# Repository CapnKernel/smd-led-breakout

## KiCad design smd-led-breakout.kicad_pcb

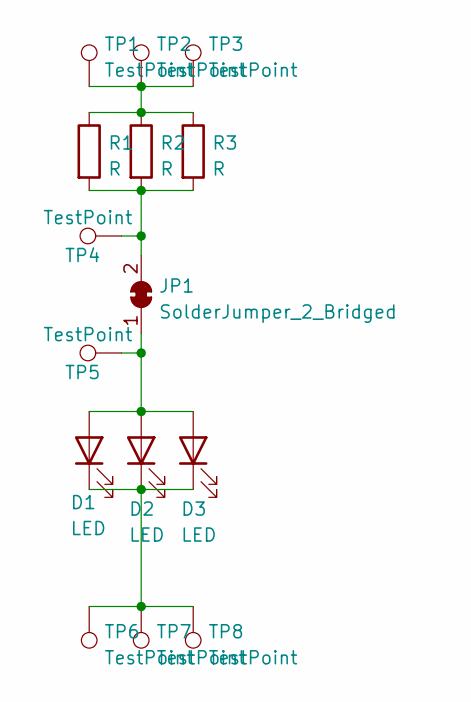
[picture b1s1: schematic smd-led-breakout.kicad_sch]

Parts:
D1: LED; LED_0603_1608Metric_Pad1.05x0.95mm_HandSolder
D2: LED; LED_0805_2012Metric_Pad1.15x1.40mm_HandSolder
D3: LED; LED_1206_3216Metric_Pad1.42x1.75mm_HandSolder
JP1: SolderJumper_2_Bridged; SolderJumper-2_P1.3mm_Bridged_Pad1.0x1.5mm
R1: R; R_0603_1608Metric_Pad0.98x0.95mm_HandSolder
R2: R; R_0805_2012Metric_Pad1.20x1.40mm_HandSolder
R3: R; R_1206_3216Metric_Pad1.30x1.75mm_HandSolder
TP1, TP2, TP3, TP4, TP5, TP6, TP7, TP8: TestPoint; Pin_D1.0mm_L10.0mm

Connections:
unnamed: D1.2 (A), D2.2 (A), D3.2 (A), JP1.1 (A), TP5.1
unnamed: D1.1 (K), D2.1 (K), D3.1 (K), TP6.1, TP7.1, TP8.1
unnamed: JP1.2 (B), R1.2, R2.2, R3.2, TP4.1
unnamed: R1.1, R2.1, R3.1, TP1.1, TP2.1, TP3.1

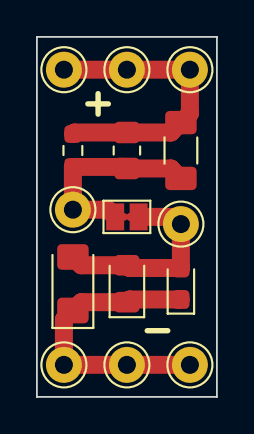
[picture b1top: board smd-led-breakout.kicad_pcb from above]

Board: 2 copper layers, 10.0 x 20.0 mm, 15 parts (0 on the bottom side), 4 nets.

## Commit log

2022-11-10 A git ignore for KiCad projects.
2022-11-10 Version 0.1, sent off.
2022-11-11 Added bridge for measuring current.
2023-05-10 Refinements
